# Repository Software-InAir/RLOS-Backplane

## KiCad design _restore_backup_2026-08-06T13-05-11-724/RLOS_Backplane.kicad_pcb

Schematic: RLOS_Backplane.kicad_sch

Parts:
+24: TMS-101-51-G-D; SAMTEC_TMS-101-51-G-D
C1, C5: C0805C104M5RACTU; CAPC2012X88N
C2: CGA4J3X5R1V225K125AB; CAPC2012X145N
C3, C7: GRM32ER61C476KE15L; CAPC3225X270N
C4: VJ0805A820JXACW1BC; CAPC2012X70N
C6: C1608X5R1V335K080AC; CAPC1608X100N
C8: GRM1555C1E470JA01D; CAPC1005X55N
C9, C10: GQM2195C1H270JB01D; CAPC2012X88N
C11, C12: GRM1555C1H6R2CA01D; CAPC1005X55N
C13, C14, C15, C16, C17, C18, C19, C20, C21, C22, C23, C24, C25, C26, C27: GRM155R71C104KA88J; CAPC1005X55N
J1: FTSH-105-01-X-DV-P-K-X; SAMTEC_FTSH-105-01-X-DV-P-K-X; PARTREV H
J4: TMS-101-51-G-D; SAMTEC_TMS-101-51-G-D
J7, J8, J9, J10, J11, J12, J13, J14: 5106726-1; CONN_5100147-1_TYC
L1: NPI31W100MTRF; IND_NPI31_NIC
L2: NPI43C4R7MTRF; IND_NPI43C_NIC
R1: CRCW040213K7FKED; RESC1005X40N
R2, R3: CRCW0402100KFKED; RESC1005X40N
R4: CRCW040222K1FKED; RESC1005X40N
R5: CRCW040210K0FKEDC; RESC1005X35N
R6, R7, R8, R9, R10, R11, R12, R13, R14, R15, R16, R17, R18, R19, R20, R21: CRT0402-BY-1002GLF; RESC1005X35N
U1: STM32H743ZIT6; QFP50P2200X2200X160-144N; PARTREV 7
U2: TPS543021DRLR; DRL0006A-MFG
U3: TPS54202DDC; SOT95P280X110-6N
U4, U6, U7, U8, U9, U10, U11, U12: TCA6424ARGJR; QFN50P500X500X60-33N
U5: TCA9548APWR; SOP65P640X120-24N; PARTREV G
Y1: ABS07-LR-32.768KHZ-6-1-T; XTAL320X150X90
Y2: C3E-8.000-18-3030-X-R; XTAL_C3E-8.000-18-3030-X-R; PARTREV August 01, 2022

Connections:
+3V3: C7.1, C8.1, C13.1, C14.1, C15.1, C16.1, C17.1, C18.1, C19.1, C20.1, C21.1, C22.1, C23.1, C24.1, C25.1, C26.1, C27.1, J1.01, J7.A25, J7.B25, J8.A25, J8.B25, J9.A25, J9.B25, J10.A25, J10.B25, J11.A25, J11.B25, J12.A25, J12.B25, J13.A25, J13.B25, J14.A25, J14.B25, L2.1, R3.1, R5.2, R6.2, R7.2, R8.2, R9.2, R10.2, R11.2, R12.2, R13.2, R14.2, R15.2, R16.2, R17.2, R18.2, R19.2, R20.2, R21.2, U1.6 (VBAT), U1.17 (VDD), U1.30 (VDD), U1.39 (VDD), U1.52 (VDD), U1.62 (VDD), U1.72 (VDD), U1.84 (VDD), U1.95 (VDD33USB), U1.108 (VDD), U1.121 (VDD), U1.131 (VDD), U1.144 (VDD), U4.27 (VCCP), U4.31 (VCCI), U5.24 (VCC), U6.27 (VCCP), U6.31 (VCCI), U7.27 (VCCP), U7.31 (VCCI), U8.27 (VCCP), U8.31 (VCCI), U9.27 (VCCP), U9.31 (VCCI), U10.27 (VCCP), U10.31 (VCCI), U11.27 (VCCP), U11.31 (VCCI), U12.27 (VCCP), U12.31 (VCCI)
+5V: C3.1, C4.1, C6.1, J4.01 (+5V), J7.A15, J7.B15, J7.C15, J8.A15, J8.B15, J8.C15, J9.A15, J9.B15, J9.C15, J10.A15, J10.B15, J10.C15, J11.A15, J11.B15, J11.C15, J12.A15, J12.B15, J12.C15, J13.A15, J13.B15, J13.C15, J14.A15, J14.B15, J14.C15, L1.2, R2.1, U3.3 (VIN); also elsewhere on the board
GND: +24.02 (-_02), C2.2, C3.2, C6.2, C7.2, C9.2, C10.2, C11.2, C12.2, C13.2, C14.2, C15.2, C16.2, C17.2, C18.2, C19.2, C20.2, C21.2, C22.2, C23.2, C24.2, C25.2, C26.2, C27.2, J1.03, J1.05, J1.09, J4.02 (-), R1.2, R4.2, U1.16 (VSS), U1.31 (VSSA), U1.38 (VSS), U1.51 (VSS), U1.61 (VSS), U1.83 (VSS), U1.94 (VSS), U1.107 (VSS), U1.120 (VSS), U1.130 (VSS), U2.1 (GND), U3.1 (GND), U4.25 (GND), U4.26 (ADDR), U4.33 (EXP), U5.1 (A0), U5.2 (A1), U5.12 (GND), U5.21 (A2), U6.25 (GND), U6.26 (ADDR), U6.33 (EXP), U7.25 (GND), U7.26 (ADDR), U7.33 (EXP), U8.25 (GND), U8.26 (ADDR), U8.33 (EXP), U9.25 (GND), U9.26 (ADDR), U9.33 (EXP), U10.25 (GND), U10.26 (ADDR), U10.33 (EXP), U11.25 (GND), U11.26 (ADDR), U11.33 (EXP), U12.25 (GND), U12.26 (ADDR), U12.33 (EXP), Y2.2 (GND), Y2.4 (GND)
unnamed: J10.D6, U1.34 (PA0)
unnamed: J10.C6, U1.35 (PA1)
unnamed: U1.36 (PA2), U5.3 (~RESET)
unnamed: J7.D3, J8.D3, U1.41 (PA5)
unnamed: J7.B3, J8.B3, U1.42 (PA6)
unnamed: J7.C3, J8.C3, U1.43 (PA7)
unnamed: U1.100 (PA8), U5.22 (SCL)
unnamed: J1.02, U1.105 (PA13(JTMS-SWDIO))
unnamed: J1.04, U1.109 (PA14(JTCK/SWCLK))
unnamed: C9.1, U1.23 (PH0/OSC_IN), Y2.1
unnamed: C10.1, U1.24 (PH1/OSC_OUT), Y2.3
unnamed: J1.10, R5.1, U1.25 (~RST)
unnamed: J13.B6, U1.46 (PB0)
unnamed: J14.B6, U1.47 (PB1)
unnamed: J9.C3, J10.C3, U1.48 (PB2)
unnamed: J7.D6, U1.136 (PB6)
unnamed: J7.C6, U1.137 (PB7)
unnamed: J7.D5, J8.D5, J9.D5, J10.D5, J11.D5, J12.D5, J13.D5, J14.D5, U1.139 (PB8)
unnamed: J7.C5, J8.C5, J9.C5, J10.C5, J11.C5, J12.C5, J13.C5, J14.C5, U1.140 (PB9)
unnamed: J12.C7, U1.69 (PB10)
unnamed: J12.B7, U1.70 (PB11)
unnamed: J13.D4, U1.73 (PB12)
unnamed: J13.D3, J14.D3, U1.74 (PB13)
unnamed: J13.B3, J14.B3, U1.75 (PB14)
unnamed: J13.C3, J14.C3, U1.76 (PB15)
unnamed: J7.B6, U1.26 (PC0)
unnamed: J8.B6, U1.27 (PC1)
unnamed: J9.B6, U1.28 (PC2_C)
unnamed: J10.B6, U1.29 (PC3_C)
unnamed: J11.B6, U1.44 (PC4)
unnamed: J12.B6, U1.45 (PC5)
unnamed: J12.D6, U1.96 (PC6)
unnamed: J12.C6, U1.97 (PC7)
unnamed: U1.99 (PC9), U5.23 (SDA)
unnamed: J9.D3, J10.D3, U1.111 (PC10)
unnamed: J9.B3, J10.B3, U1.112 (PC11)
unnamed: J11.D6, U1.113 (PC12)
unnamed: J14.B7, U1.7 (PC13)
unnamed: C11.1, U1.8 (PC14/OSC32_IN), Y1.1
unnamed: C12.1, U1.9 (PC15/OSC32_OUT), Y1.2
unnamed: J13.B4, U1.114 (PD0)
unnamed: J13.B5, U1.115 (PD1)
unnamed: J11.C6, U1.116 (PD2)
unnamed: J13.D7, U1.117 (PD3)
unnamed: J13.C7, U1.118 (PD4)
unnamed: J8.D6, U1.119 (PD5)
unnamed: J8.C6, U1.122 (PD6)
unnamed: J13.B7, U1.123 (PD7)
unnamed: J9.D6, U1.77 (PD8)
unnamed: J9.C6, U1.78 (PD9)
unnamed: J14.D4, U1.79 (PD10)
unnamed: J14.C4, U1.80 (PD11)
unnamed: J14.B4, U1.81 (PD12)
unnamed: J14.B5, U1.82 (PD13)
unnamed: J14.D7, U1.85 (PD14)
unnamed: J14.C7, U1.86 (PD15)
unnamed: J14.C6, U1.141 (PE0)
unnamed: J14.D6, U1.142 (PE1)
unnamed: J11.D7, U1.1 (PE2)
unnamed: J11.C7, U1.2 (PE3)
unnamed: J11.B7, U1.3 (PE4)
unnamed: J12.D4, U1.4 (PE5)
unnamed: J12.C4, U1.5 (PE6)
unnamed: J13.C6, U1.58 (PE7)
unnamed: J13.D6, U1.59 (PE8)
unnamed: J12.B4, U1.60 (PE9)
unnamed: J12.B5, U1.63 (PE10)
unnamed: J11.D3, J12.D3, U1.65 (PE12)
unnamed: J11.B3, J12.B3, U1.66 (PE13)
unnamed: J11.C3, J12.C3, U1.67 (PE14)
unnamed: J13.C4, U1.68 (PE15)
unnamed: J9.B4, U1.10 (PF0)
unnamed: J9.B5, U1.11 (PF1)
unnamed: J9.D7, U1.12 (PF2)
unnamed: J9.C7, U1.13 (PF3)
unnamed: J9.B7, U1.14 (PF4)
unnamed: J10.D4, U1.15 (PF5)
unnamed: J10.C4, U1.18 (PF6)
unnamed: J10.B4, U1.19 (PF7)
unnamed: J10.B5, U1.20 (PF8)
unnamed: J10.D7, U1.21 (PF9)
unnamed: J10.C7, U1.22 (PF10)
unnamed: J10.B7, U1.49 (PF11)
unnamed: J11.D4, U1.50 (PF12)
unnamed: J11.C4, U1.53 (PF13)
unnamed: J11.B4, U1.54 (PF14)
unnamed: J11.B5, U1.55 (PF15)
unnamed: J7.D4, U1.56 (PG0)
unnamed: J7.C4, U1.57 (PG1)
unnamed: J7.B4, U1.87 (PG2)
unnamed: J7.B5, U1.88 (PG3)
unnamed: J7.D7, U1.89 (PG4)
unnamed: J7.C7, U1.90 (PG5)
unnamed: J7.B7, U1.91 (PG6)
unnamed: J8.D4, U1.92 (PG7)
unnamed: J8.C4, U1.93 (PG8)
unnamed: J8.B4, U1.124 (PG9)
unnamed: J8.B5, U1.125 (PG10)
unnamed: J8.D7, U1.126 (PG11)
unnamed: J8.C7, U1.127 (PG12)
unnamed: J8.B7, U1.128 (PG13)
unnamed: J9.D4, U1.129 (PG14)
unnamed: J9.C4, U1.132 (PG15)
unnamed: C1.1, U2.6 (BOOT)
unnamed: C4.2, R1.1, R2.2, U2.4 (FB)
unnamed: C1.2, L1.1, U2.2 (SW)
unnamed: +24.+, C2.1, J7.A1, J7.A2, J7.B1, J7.B2, J8.A1, J8.A2, J8.B1, J8.B2, J9.A1, J9.A2, J9.B1, J9.B2, J10.A1, J10.A2, J10.B1, J10.B2, J11.A1, J11.A2, J11.B1, J11.B2, J12.A1, J12.A2, J12.B1, J12.B2, J13.A1, J13.A2, J13.B1, J13.B2, J14.A1, J14.A2, J14.B1, J14.B2, U2.3 (VIN)
unnamed: C5.1, U3.6 (BOOT)
unnamed: C8.2, R3.2, R4.1, U3.4 (FB)
unnamed: C5.2, L2.2, U3.2 (SW)
unnamed: J7.D9, U4.1 (P00)
unnamed: J7.C9, U4.2 (P01)
unnamed: J7.B9, U4.3 (P02)
unnamed: J7.A9, U4.4 (P03)
unnamed: J7.D10, U4.5 (P04)
unnamed: J7.C10, U4.6 (P05)
unnamed: J7.B10, U4.7 (P06)
unnamed: J7.A10, U4.8 (P07)
unnamed: J7.D11, U4.9 (P10)
unnamed: J7.C11, U4.10 (P11)
unnamed: J7.B11, U4.11 (P12)
unnamed: J7.A11, U4.12 (P13)
unnamed: J7.D16, U4.13 (P14)
unnamed: J7.C16, U4.14 (P15)
unnamed: J7.B16, U4.15 (P16)
unnamed: J7.A16, U4.16 (P17)
unnamed: J7.D17, U4.17 (P20)
unnamed: J7.C17, U4.18 (P21)
unnamed: J7.B17, U4.19 (P22)
unnamed: J7.A17, U4.20 (P23)
unnamed: J7.D18, U4.21 (P24)
unnamed: J7.C18, U4.22 (P25)
unnamed: J7.B18, U4.23 (P26)
unnamed: J7.A18, U4.24 (P27)
unnamed: U4.29 (SCL), U5.5 (SC0)
unnamed: U4.30 (SDA), U5.4 (SD0)
unnamed: R7.1, U4.32 (~INT)
unnamed: R6.1, U4.28 (~RESET)
unnamed: U5.7 (SC1), U6.29 (SCL)
unnamed: U5.9 (SC2), U7.29 (SCL)
unnamed: U5.11 (SC3), U8.29 (SCL)
unnamed: U5.14 (SC4), U9.29 (SCL)
unnamed: U5.6 (SD1), U6.30 (SDA)
unnamed: U5.8 (SD2), U7.30 (SDA)
unnamed: U5.10 (SD3), U8.30 (SDA)
unnamed: U5.13 (SD4), U9.30 (SDA)
unnamed: J8.D9, U6.1 (P00)
unnamed: J8.C9, U6.2 (P01)
unnamed: J8.B9, U6.3 (P02)
unnamed: J8.A9, U6.4 (P03)
unnamed: J8.D10, U6.5 (P04)
unnamed: J8.C10, U6.6 (P05)
unnamed: J8.B10, U6.7 (P06)
unnamed: J8.A10, U6.8 (P07)
unnamed: J8.D11, U6.9 (P10)
unnamed: J8.C11, U6.10 (P11)
unnamed: J8.B11, U6.11 (P12)
unnamed: J8.A11, U6.12 (P13)
unnamed: J8.D16, U6.13 (P14)
unnamed: J8.C16, U6.14 (P15)
unnamed: J8.B16, U6.15 (P16)
unnamed: J8.A16, U6.16 (P17)
unnamed: J8.D17, U6.17 (P20)
unnamed: J8.C17, U6.18 (P21)
unnamed: J8.B17, U6.19 (P22)
unnamed: J8.A17, U6.20 (P23)
unnamed: J8.D18, U6.21 (P24)
unnamed: J8.C18, U6.22 (P25)
unnamed: J8.B18, U6.23 (P26)
unnamed: J8.A18, U6.24 (P27)
unnamed: R9.1, U6.32 (~INT)
unnamed: R8.1, U6.28 (~RESET)
unnamed: J9.D9, U7.1 (P00)
unnamed: J9.C9, U7.2 (P01)
unnamed: J9.B9, U7.3 (P02)
unnamed: J9.A9, U7.4 (P03)
unnamed: J9.D10, U7.5 (P04)
unnamed: J9.C10, U7.6 (P05)
unnamed: J9.B10, U7.7 (P06)
unnamed: J9.A10, U7.8 (P07)
unnamed: J9.D11, U7.9 (P10)
unnamed: J9.C11, U7.10 (P11)
unnamed: J9.B11, U7.11 (P12)
unnamed: J9.A11, U7.12 (P13)
unnamed: J9.D16, U7.13 (P14)
unnamed: J9.C16, U7.14 (P15)
unnamed: J9.B16, U7.15 (P16)
unnamed: J9.A16, U7.16 (P17)
unnamed: J9.D17, U7.17 (P20)
unnamed: J9.C17, U7.18 (P21)
unnamed: J9.B17, U7.19 (P22)
unnamed: J9.A17, U7.20 (P23)
unnamed: J9.D18, U7.21 (P24)
unnamed: J9.C18, U7.22 (P25)
unnamed: J9.B18, U7.23 (P26)
unnamed: J9.A18, U7.24 (P27)
unnamed: R11.1, U7.32 (~INT)
unnamed: R10.1, U7.28 (~RESET)
unnamed: J10.D9, U8.1 (P00)
unnamed: J10.C9, U8.2 (P01)
unnamed: J10.B9, U8.3 (P02)
unnamed: J10.A9, U8.4 (P03)
unnamed: J10.D10, U8.5 (P04)
unnamed: J10.C10, U8.6 (P05)
unnamed: J10.B10, U8.7 (P06)
unnamed: J10.A10, U8.8 (P07)
unnamed: J10.D11, U8.9 (P10)
unnamed: J10.C11, U8.10 (P11)
unnamed: J10.B11, U8.11 (P12)
unnamed: J10.A11, U8.12 (P13)
unnamed: J10.D16, U8.13 (P14)
unnamed: J10.C16, U8.14 (P15)
unnamed: J10.B16, U8.15 (P16)
unnamed: J10.A16, U8.16 (P17)
unnamed: J10.D17, U8.17 (P20)
unnamed: J10.C17, U8.18 (P21)
unnamed: J10.B17, U8.19 (P22)
unnamed: J10.A17, U8.20 (P23)
unnamed: J10.D18, U8.21 (P24)
unnamed: J10.C18, U8.22 (P25)
unnamed: J10.B18, U8.23 (P26)
unnamed: J10.A18, U8.24 (P27)
unnamed: R13.1, U8.32 (~INT)
unnamed: R12.1, U8.28 (~RESET)
unnamed: J11.D9, U9.1 (P00)
unnamed: J11.C9, U9.2 (P01)
unnamed: J11.B9, U9.3 (P02)
unnamed: J11.A9, U9.4 (P03)
unnamed: J11.D10, U9.5 (P04)
unnamed: J11.C10, U9.6 (P05)
unnamed: J11.B10, U9.7 (P06)
unnamed: J11.A10, U9.8 (P07)
unnamed: J11.D11, U9.9 (P10)
unnamed: J11.C11, U9.10 (P11)
unnamed: J11.B11, U9.11 (P12)
unnamed: J11.A11, U9.12 (P13)
unnamed: J11.D16, U9.13 (P14)
unnamed: J11.C16, U9.14 (P15)
unnamed: J11.B16, U9.15 (P16)
unnamed: J11.A16, U9.16 (P17)
unnamed: J11.D17, U9.17 (P20)
unnamed: J11.C17, U9.18 (P21)
unnamed: J11.B17, U9.19 (P22)
unnamed: J11.A17, U9.20 (P23)
unnamed: J11.D18, U9.21 (P24)
unnamed: J11.C18, U9.22 (P25)
unnamed: J11.B18, U9.23 (P26)
unnamed: J11.A18, U9.24 (P27)
unnamed: R15.1, U9.32 (~INT)
unnamed: R14.1, U9.28 (~RESET)
unnamed: J12.D9, U10.1 (P00)
unnamed: J12.C9, U10.2 (P01)
unnamed: J12.B9, U10.3 (P02)
unnamed: J12.A9, U10.4 (P03)
unnamed: J12.D10, U10.5 (P04)
unnamed: J12.C10, U10.6 (P05)
unnamed: J12.B10, U10.7 (P06)
unnamed: J12.A10, U10.8 (P07)
unnamed: J12.D11, U10.9 (P10)
unnamed: J12.C11, U10.10 (P11)
unnamed: J12.B11, U10.11 (P12)
unnamed: J12.A11, U10.12 (P13)
unnamed: J12.D16, U10.13 (P14)
unnamed: J12.C16, U10.14 (P15)
unnamed: J12.B16, U10.15 (P16)
unnamed: J12.A16, U10.16 (P17)
unnamed: J12.D17, U10.17 (P20)
unnamed: J12.C17, U10.18 (P21)
unnamed: J12.B17, U10.19 (P22)
unnamed: J12.A17, U10.20 (P23)
unnamed: J12.D18, U10.21 (P24)
unnamed: J12.C18, U10.22 (P25)
unnamed: J12.B18, U10.23 (P26)
unnamed: J12.A18, U10.24 (P27)
unnamed: U5.16 (SC5), U10.29 (SCL)
unnamed: U5.15 (SD5), U10.30 (SDA)
unnamed: R17.1, U10.32 (~INT)
unnamed: R16.1, U10.28 (~RESET)
unnamed: J13.D9, U11.1 (P00)
unnamed: J13.C9, U11.2 (P01)
unnamed: J13.B9, U11.3 (P02)
unnamed: J13.A9, U11.4 (P03)
unnamed: J13.D10, U11.5 (P04)
unnamed: J13.C10, U11.6 (P05)
unnamed: J13.B10, U11.7 (P06)
unnamed: J13.A10, U11.8 (P07)
unnamed: J13.D11, U11.9 (P10)
unnamed: J13.C11, U11.10 (P11)
unnamed: J13.B11, U11.11 (P12)
unnamed: J13.A11, U11.12 (P13)
unnamed: J13.D16, U11.13 (P14)
unnamed: J13.C16, U11.14 (P15)
unnamed: J13.B16, U11.15 (P16)
unnamed: J13.A16, U11.16 (P17)
unnamed: J13.D17, U11.17 (P20)
unnamed: J13.C17, U11.18 (P21)
unnamed: J13.B17, U11.19 (P22)
unnamed: J13.A17, U11.20 (P23)
unnamed: J13.D18, U11.21 (P24)
unnamed: J13.C18, U11.22 (P25)
unnamed: J13.B18, U11.23 (P26)
unnamed: J13.A18, U11.24 (P27)
unnamed: U5.18 (SC6), U11.29 (SCL)
unnamed: U5.17 (SD6), U11.30 (SDA)
unnamed: R19.1, U11.32 (~INT)
unnamed: R18.1, U11.28 (~RESET)
unnamed: J14.D9, U12.1 (P00)
unnamed: J14.C9, U12.2 (P01)
unnamed: J14.B9, U12.3 (P02)
unnamed: J14.A9, U12.4 (P03)
unnamed: J14.D10, U12.5 (P04)
unnamed: J14.C10, U12.6 (P05)
unnamed: J14.B10, U12.7 (P06)
unnamed: J14.A10, U12.8 (P07)
unnamed: J14.D11, U12.9 (P10)
unnamed: J14.C11, U12.10 (P11)
unnamed: J14.B11, U12.11 (P12)
unnamed: J14.A11, U12.12 (P13)
unnamed: J14.D16, U12.13 (P14)
unnamed: J14.C16, U12.14 (P15)
unnamed: J14.B16, U12.15 (P16)
unnamed: J14.A16, U12.16 (P17)
unnamed: J14.D17, U12.17 (P20)
unnamed: J14.C17, U12.18 (P21)
unnamed: J14.B17, U12.19 (P22)
unnamed: J14.A17, U12.20 (P23)
unnamed: J14.D18, U12.21 (P24)
unnamed: J14.C18, U12.22 (P25)
unnamed: J14.B18, U12.23 (P26)
unnamed: J14.A18, U12.24 (P27)
unnamed: U5.20 (SC7), U12.29 (SCL)
unnamed: U5.19 (SD7), U12.30 (SDA)
unnamed: R21.1, U12.32 (~INT)
unnamed: R20.1, U12.28 (~RESET)
VCAP: U1.71 (VCAP), U1.106 (VCAP)

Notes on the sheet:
PH_1
DRDY
C_PRES
-VAUX
+3V3
DGND
UART RTS / RS-485 DE
IRQ
AGND
USART2 RX
+24V
Card Present
Card Reset
C_FLT
C_EN
Card Fault
+VAUX
UART6_RX
+24V
SPI_CS
CHS
P_VER
Card Enable
Card Enable
USART4_TX
5V Buck
PGND
PGND
UART8_TX
CARD PRESENT
I2C1_SDA
USART4_RX
USART2 TX
UART7_RX
USART3 TX
SPI1_MOSI
3V3 Buck
UART5_TX
I2C1_SCL
SPI CS

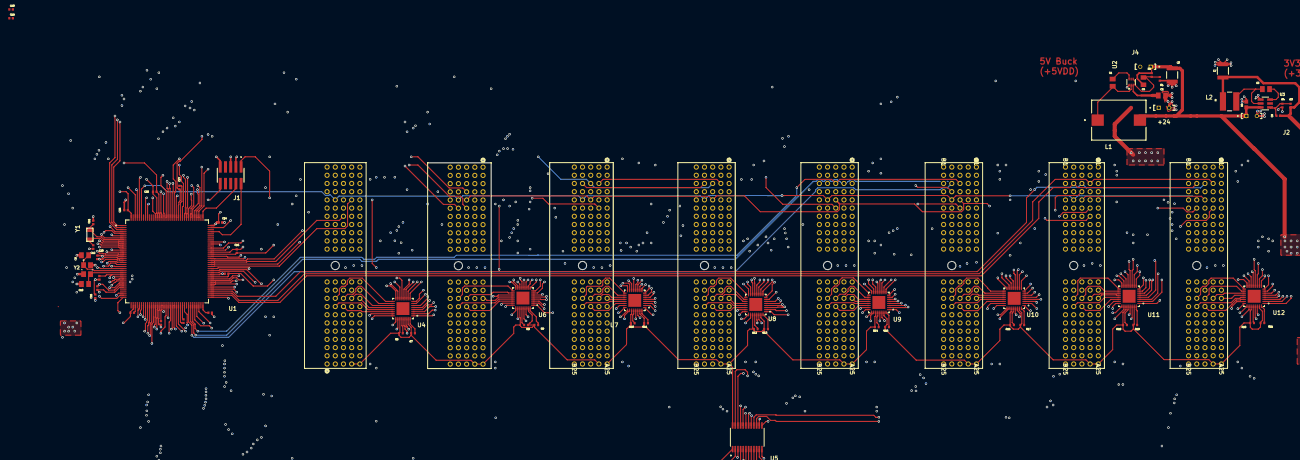
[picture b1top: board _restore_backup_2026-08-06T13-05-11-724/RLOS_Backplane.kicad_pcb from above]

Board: 8 copper layers, 76 parts (0 on the bottom side), 338 nets.

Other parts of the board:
J2: TMS-101-51-G-D; SAMTEC_TMS-101-51-G-D

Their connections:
+5V: J2.01 (+5V), J2.02 (GND); also elsewhere on the board

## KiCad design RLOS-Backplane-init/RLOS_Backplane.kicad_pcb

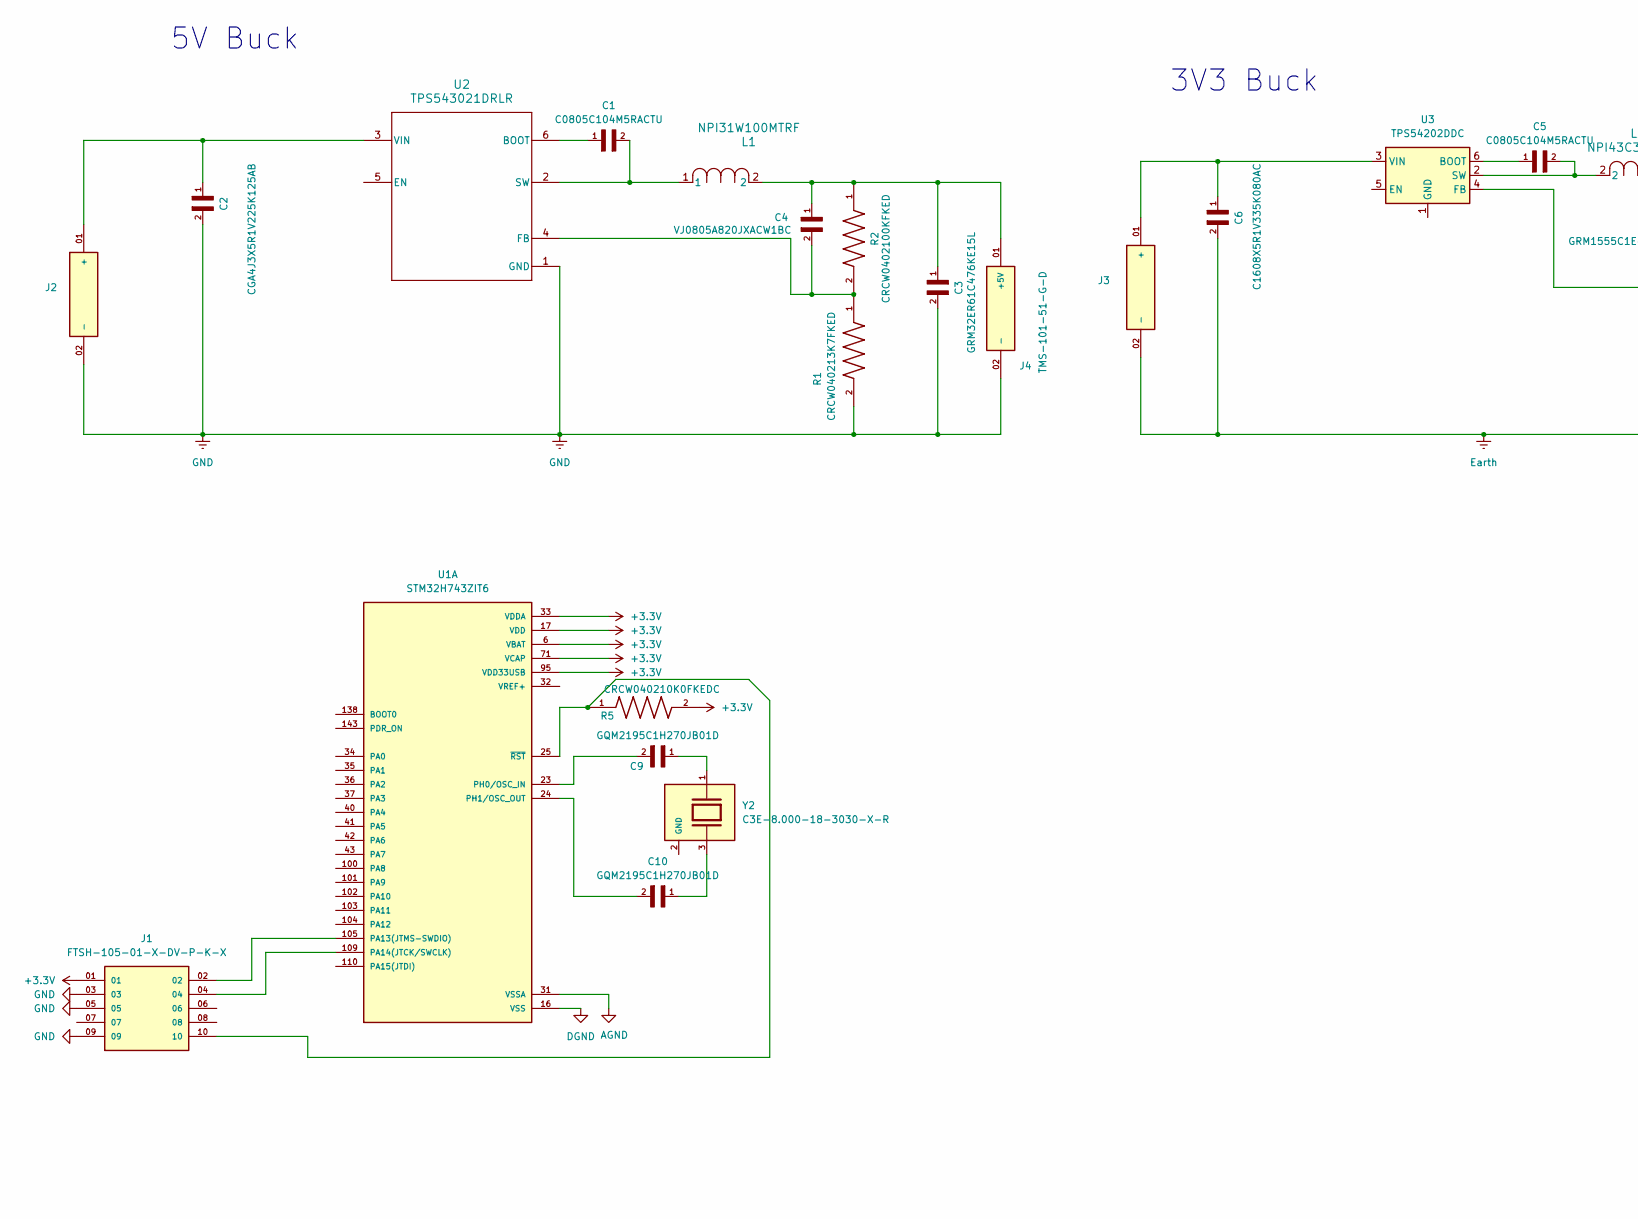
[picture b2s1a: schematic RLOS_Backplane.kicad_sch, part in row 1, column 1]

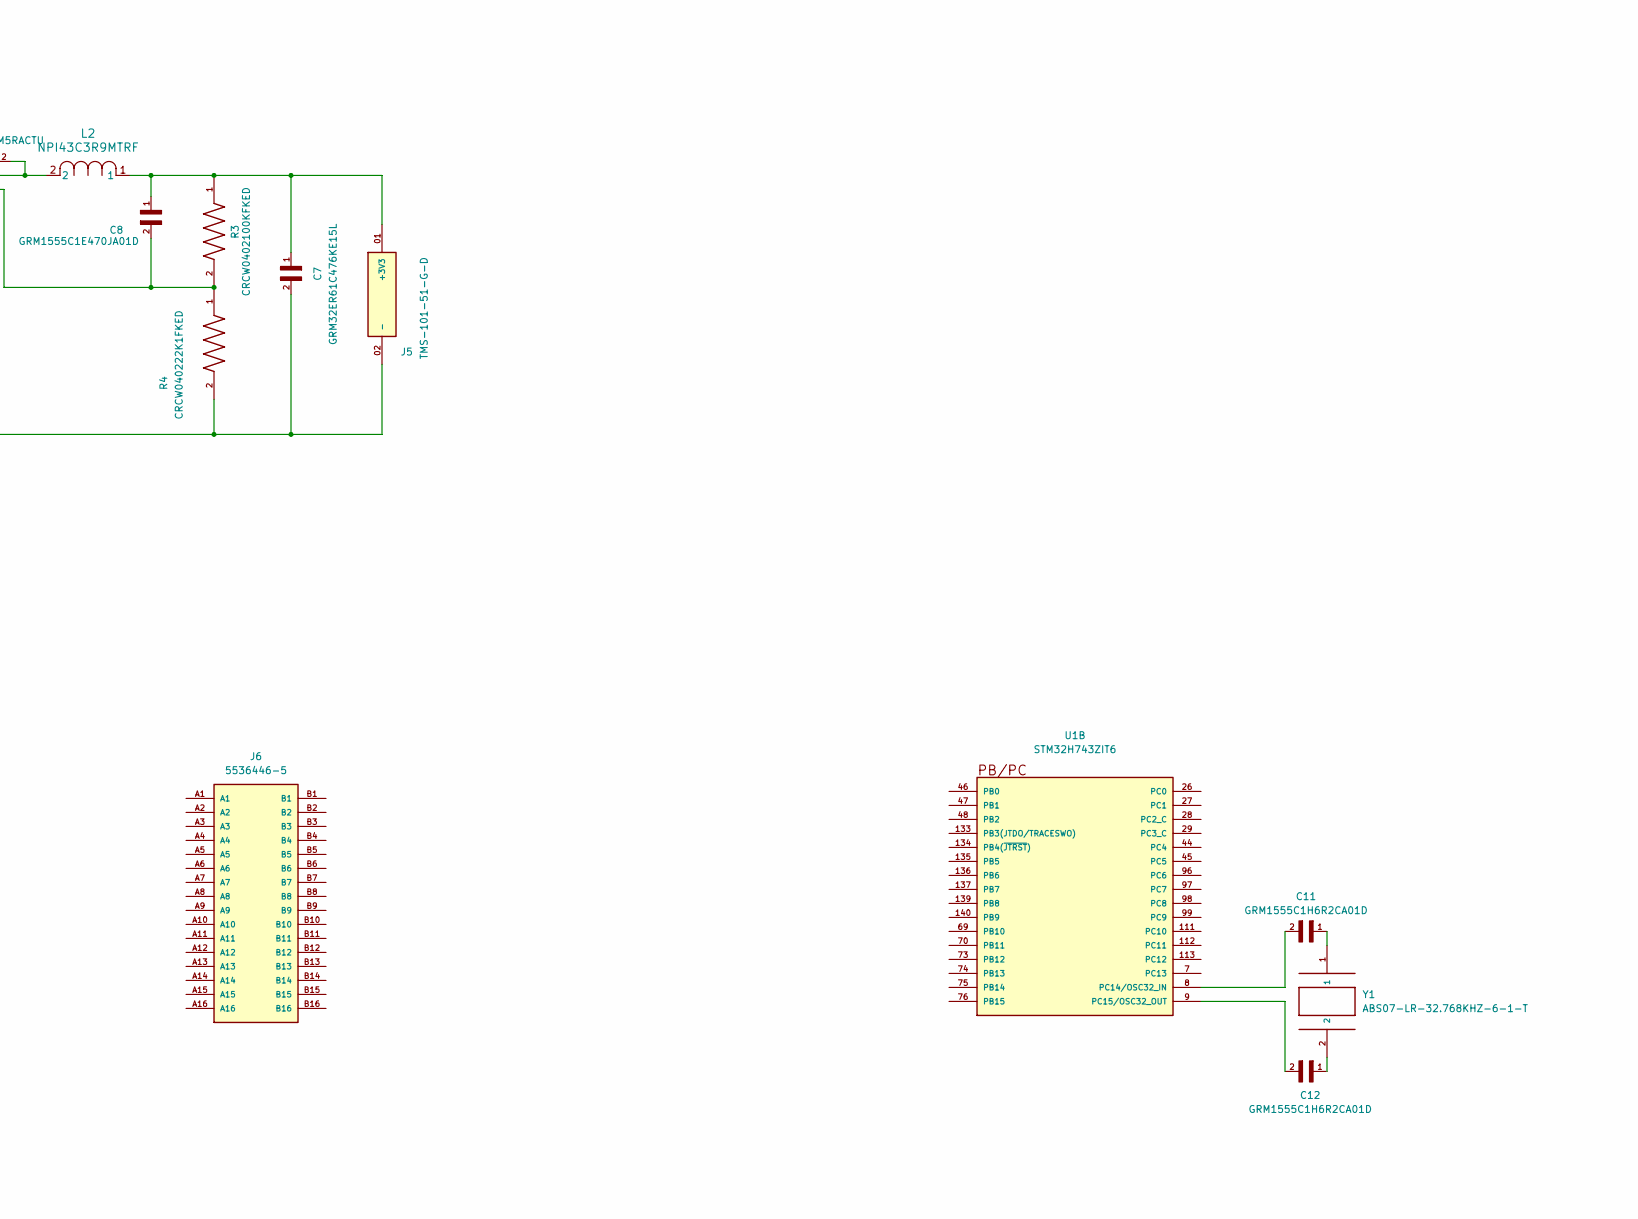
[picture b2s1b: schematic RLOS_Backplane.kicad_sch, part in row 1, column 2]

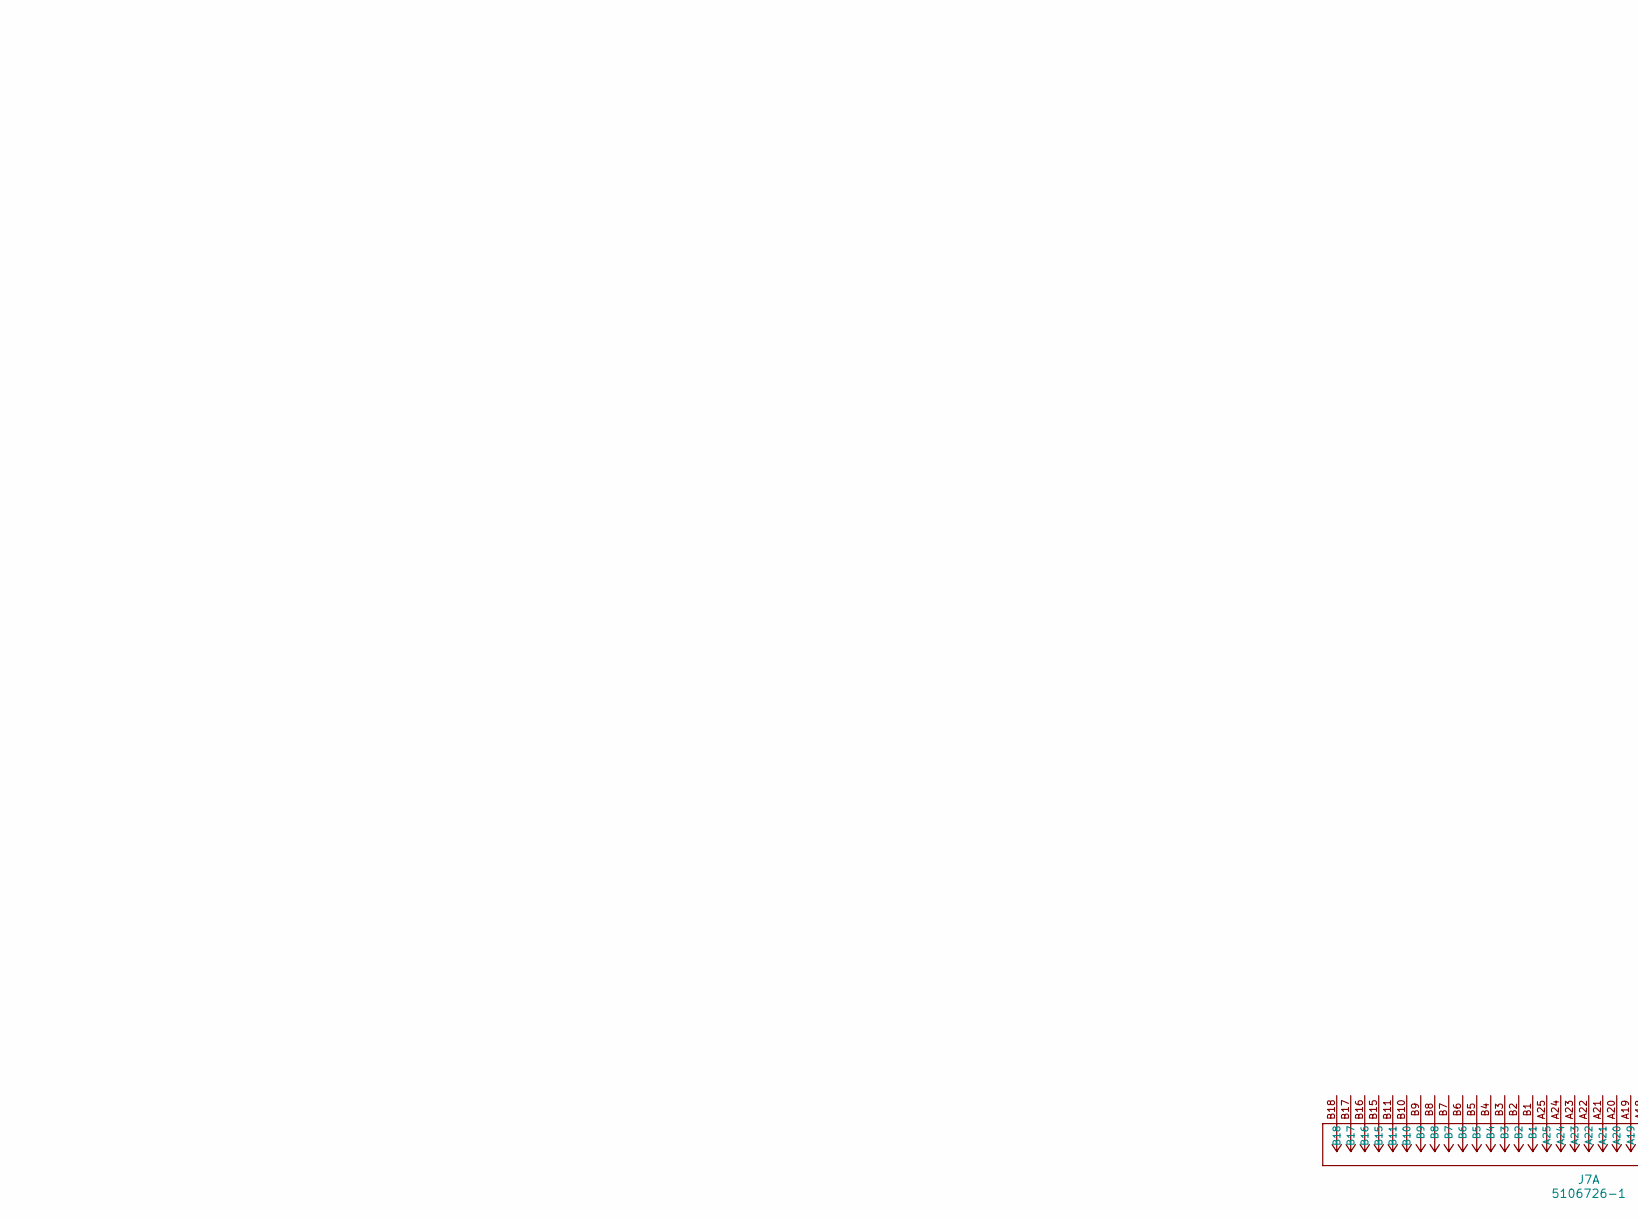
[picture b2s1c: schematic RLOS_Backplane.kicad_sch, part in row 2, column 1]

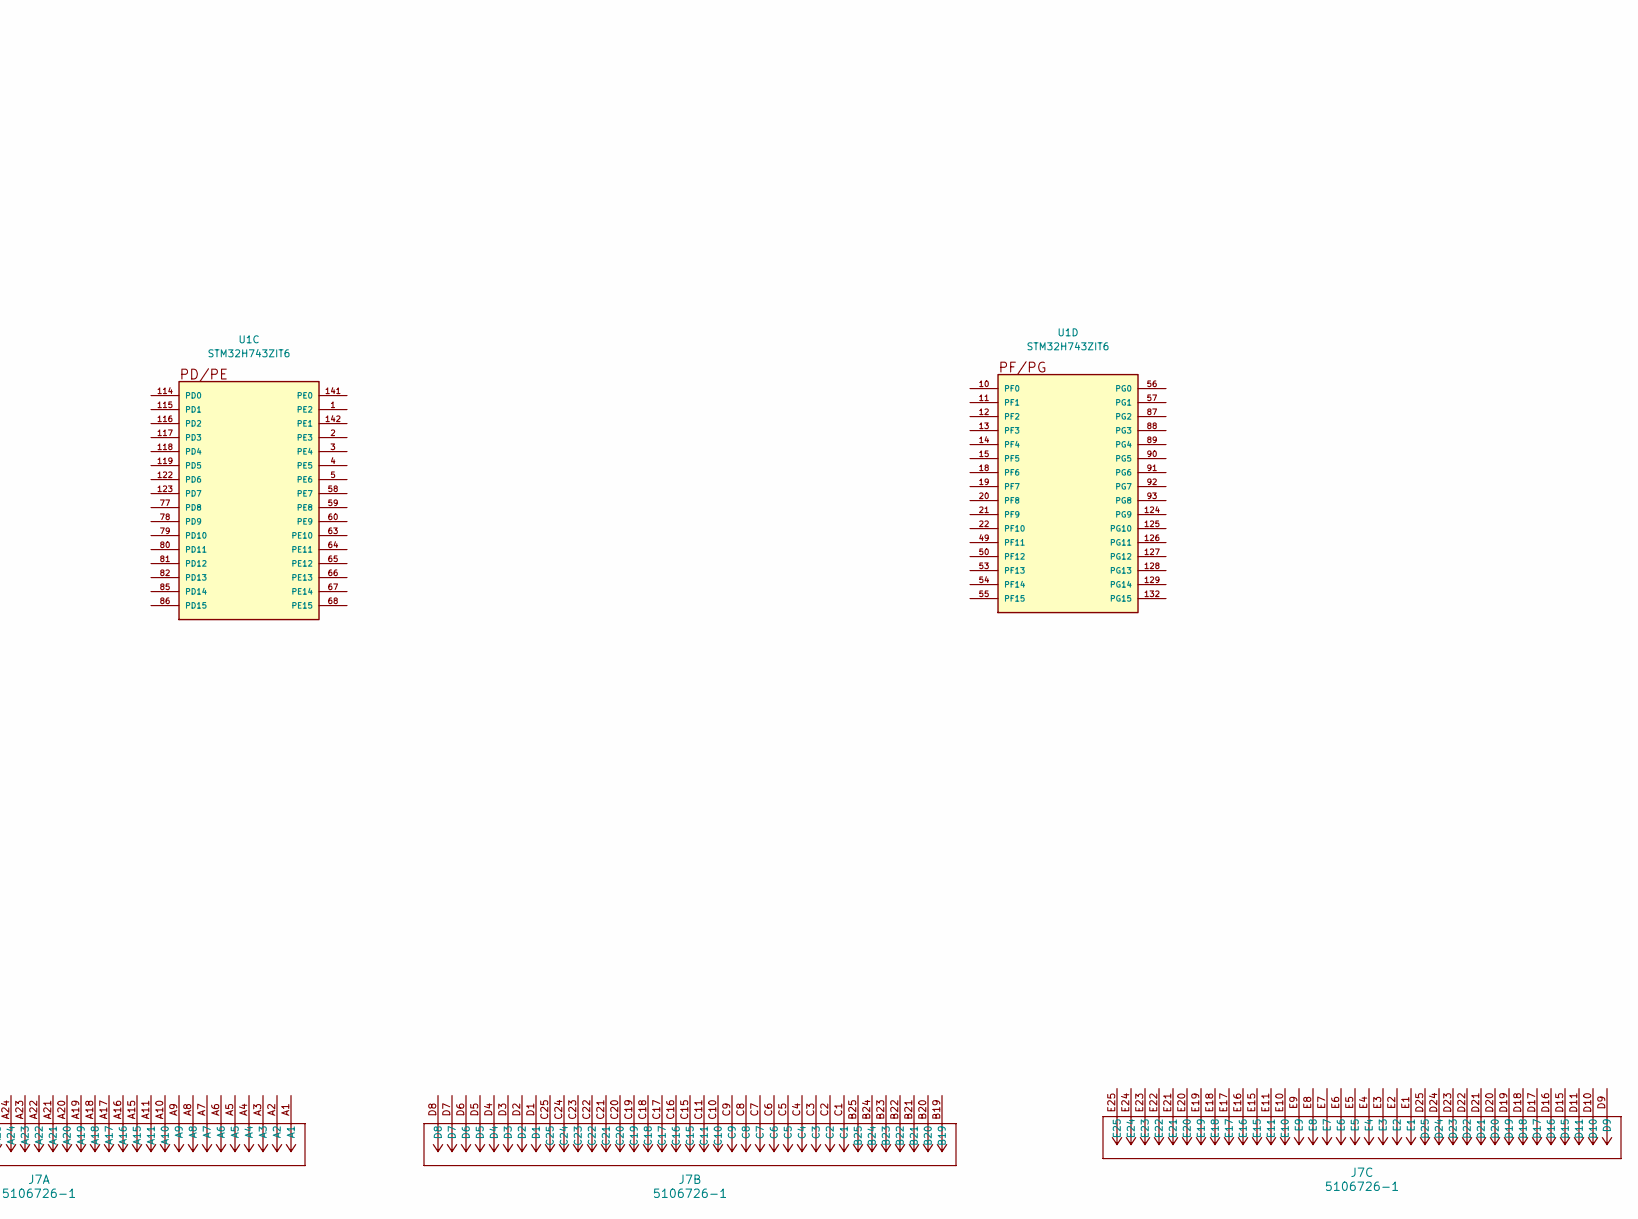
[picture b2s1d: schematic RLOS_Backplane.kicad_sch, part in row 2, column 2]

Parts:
C1, C5: C0805C104M5RACTU; CAPC2012X88N
C2: CGA4J3X5R1V225K125AB; CAPC2012X145N
C3, C7: GRM32ER61C476KE15L; CAPC3225X270N
C4: VJ0805A820JXACW1BC; CAPC2012X70N
C6: C1608X5R1V335K080AC; CAPC1608X100N
C8: GRM1555C1E470JA01D; CAPC1005X55N
C9, C10: GQM2195C1H270JB01D; CAPC2012X88N
C11, C12: GRM1555C1H6R2CA01D; CAPC1005X55N
J1: FTSH-105-01-X-DV-P-K-X; SAMTEC_FTSH-105-01-X-DV-P-K-X; PARTREV H
J2, J3, J4, J5: TMS-101-51-G-D; SAMTEC_TMS-101-51-G-D
J6: 5536446-5; TE_5536446-5; PARTREV O
J7: 5106726-1; CONN_5100147-1_TYC
L1: NPI31W100MTRF; IND_NPI31_NIC
L2: NPI43C3R9MTRF; IND_NPI43C_NIC
R1: CRCW040213K7FKED; RESC1005X40N
R2, R3: CRCW0402100KFKED; RESC1005X40N
R4: CRCW040222K1FKED; RESC1005X40N
R5: CRCW040210K0FKEDC; RESC1005X35N
U1: STM32H743ZIT6; QFP50P2200X2200X160-144N; PARTREV 7
U2: TPS543021DRLR; DRL0006A-MFG
U3: TPS54202DDC; SOT95P280X110-6N
Y1: ABS07-LR-32.768KHZ-6-1-T; XTAL320X150X90
Y2: C3E-8.000-18-3030-X-R; XTAL_C3E-8.000-18-3030-X-R; PARTREV August 01, 2022

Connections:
+3.3V: J1.01, R5.2, U1.6 (VBAT), U1.17 (VDD), U1.30 (VDD), U1.33 (VDDA), U1.39 (VDD), U1.52 (VDD), U1.62 (VDD), U1.71 (VCAP), U1.72 (VDD), U1.84 (VDD), U1.95 (VDD33USB), U1.106 (VCAP), U1.108 (VDD), U1.121 (VDD), U1.131 (VDD), U1.144 (VDD)
AGND: U1.31 (VSSA)
DGND: U1.16 (VSS), U1.38 (VSS), U1.51 (VSS), U1.61 (VSS), U1.83 (VSS), U1.94 (VSS), U1.107 (VSS), U1.120 (VSS), U1.130 (VSS)
Earth: C6.2, C7.2, J3.02 (-), J5.02 (-), R4.2
unnamed: C9.1, Y2.1
unnamed: C10.1, Y2.3
unnamed: C11.1, Y1.1
unnamed: C12.1, Y1.2
unnamed: C2.1, J2.01 (+), U2.3 (VIN)
unnamed: C6.1, J3.01 (+), U3.3 (VIN)
unnamed: C3.1, C4.1, J4.01 (+5V), L1.2, R2.1
unnamed: C7.1, C8.1, J5.01 (+3V3), L2.1, R3.1
unnamed: J1.02, U1.105 (PA13(JTMS-SWDIO))
unnamed: J1.04, U1.109 (PA14(JTCK/SWCLK))
unnamed: C9.2, U1.23 (PH0/OSC_IN)
unnamed: C10.2, U1.24 (PH1/OSC_OUT)
unnamed: J1.10, R5.1, U1.25 (~RST)
unnamed: C11.2, U1.8 (PC14/OSC32_IN)
unnamed: C12.2, U1.9 (PC15/OSC32_OUT)
unnamed: C1.1, U2.6 (BOOT)
unnamed: C4.2, R1.1, R2.2, U2.4 (FB)
unnamed: C1.2, L1.1, U2.2 (SW)
unnamed: C5.1, U3.6 (BOOT)
unnamed: C8.2, R3.2, R4.1, U3.4 (FB)
unnamed: C5.2, L2.2, U3.2 (SW)

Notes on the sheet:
5V Buck
3V3 Buck

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
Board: 2 copper layers, 31 parts (0 on the bottom side), 25 nets, no tracks yet.
